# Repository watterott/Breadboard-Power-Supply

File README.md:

# Breadboard Power Supply
Power supply for Breadboards.

* Power Input: microUSB or 2.1mm DC jack
* 5V 800mA voltage regulator
* 3.3V 800mA voltage regulator
* 3.3V or 5V output selectable with jumper
* Open-Source and released under the [Creative Commons Attribution Share-Alike License](https://creativecommons.org/licenses/by-sa/4.0/).
* **[Documentation on learn.watterott.com](https://learn.watterott.com)**

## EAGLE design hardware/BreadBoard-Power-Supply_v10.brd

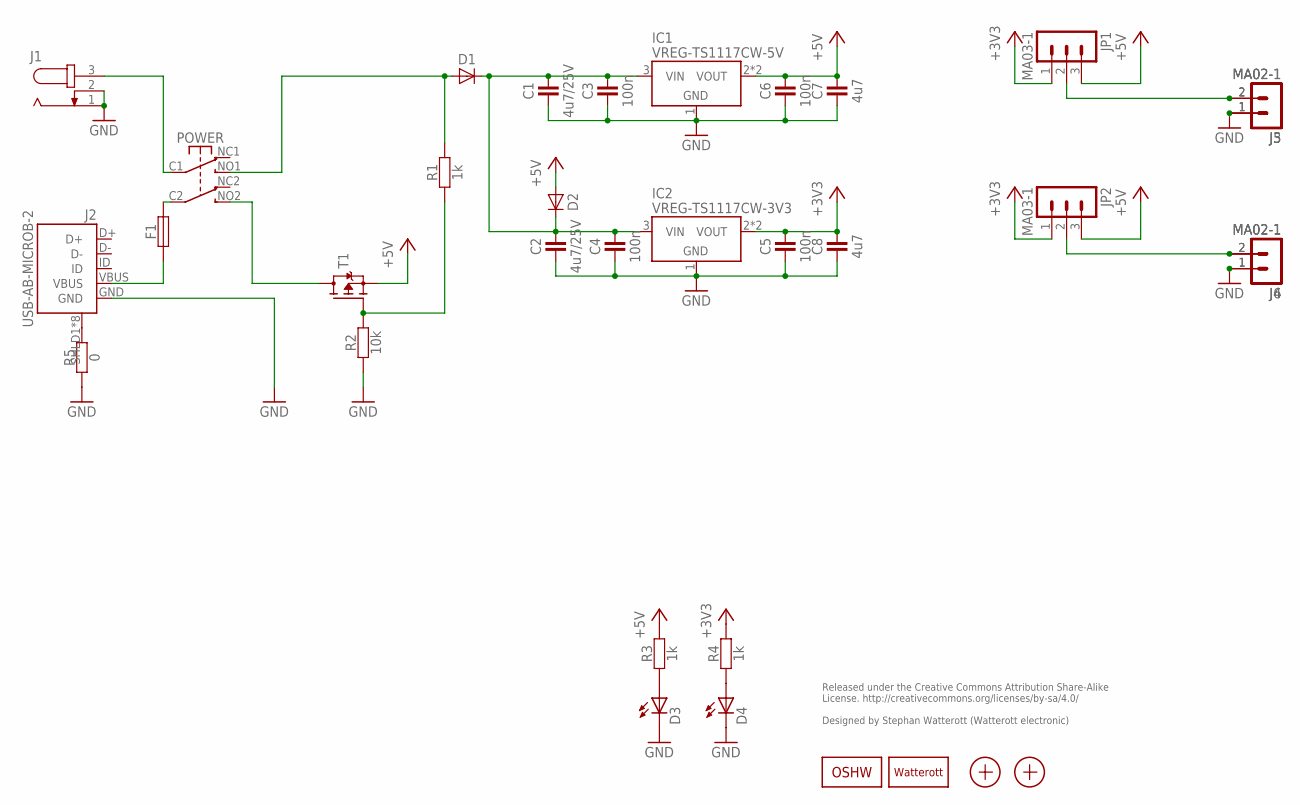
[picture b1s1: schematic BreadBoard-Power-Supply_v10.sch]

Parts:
C1, C2: 4u7/25V; C1206
C3, C4, C5, C6: 100n; C0402
C7, C8: 4u7; C0402
D1, D2: DIODE-SOD80; SOD80
D3, D4: LED-0603; C0603
F1: FUSE-0805; C0805
IC1: VREG-TS1117CW-5V; SOT223
IC2: VREG-TS1117CW-3V3; SOT223
J1: DC-JACK-2.1; DC-JACK
J2: USB-AB-MICROB-2; USB-MICROB-10118194
J3, J4, J5, J6: MA02-1
JP1, JP2: MA03-1
LOGO1: OSHW_LOGOX0070; OSHW_6X70
LOGO2: LOGO-PLACE; LOGO_TPLACE
POWER: SW-2UMGF1260159; GF1260159
R1, R3, R4: 1k; C0402
R2: 10k; C0402
R5: 0; C0402
T1: MOSFET-P-SOT23; SOT23
X1, X2: PASSER-07; PASSER_07MM

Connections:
+3V3: C5.2, C8.2, IC2.2 (VOUT), IC2.4 (VOUT), JP1.1, JP2.1, R4.2
+5V: C6.2, C7.2, D2.A, IC1.2 (VOUT), IC1.4 (VOUT), JP1.3, JP2.3, R3.2, T1.2 (S)
GND: C1.1, C2.1, C3.1, C4.1, C5.1, C6.1, C7.1, C8.1, D3.C, D4.C, IC1.1 (GND), IC2.1 (GND), J1.1, J1.2, J2.GND, J3.1, J4.1, J5.1, J6.1, R2.1, R5.1
unnamed: D1.A, POWER.NO1 (S1), R1.2
unnamed: J1.3, POWER.C1 (P1)
unnamed: R1.1, R2.2, T1.1 (G)
unnamed: POWER.NO2 (S2), T1.3 (D)
unnamed: D3.A, R3.1
unnamed: D4.A, R4.1
unnamed: J3.2, J5.2, JP1.2
unnamed: J4.2, J6.2, JP2.2
unnamed: F1.2, POWER.C2 (P2)
unnamed: J2.SHLD1 (SHIELD), J2.SHLD2 (SHIELD), J2.SHLD3 (SHIELD), J2.SHLD4 (SHIELD), J2.SHLD5 (SHIELD), J2.SHLD6 (SHIELD), J2.SHLD7 (SHIELD), J2.SHLD8 (SHIELD), R5.2
VBUS: F1.1, J2.VBUS
VIN: C1.2, C2.2, C3.2, C4.2, D1.C, D2.C, IC1.3 (VIN), IC2.3 (VIN)

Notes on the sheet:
Released under the Creative Commons Attribution Share-Alike License. http://creativecommons.org/licenses/by-sa/4.0/ Designed by Stephan Watterott (Watterott electronic)

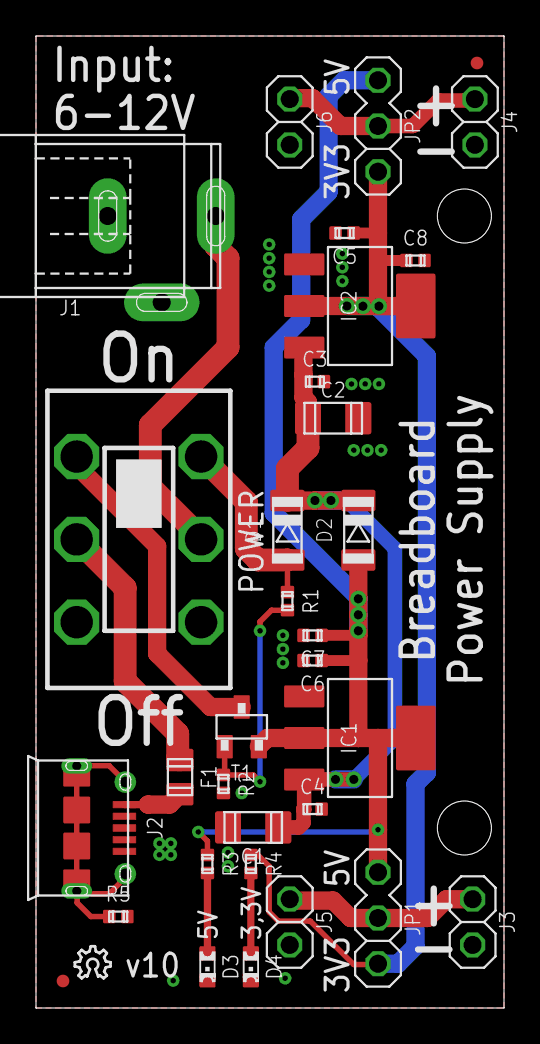
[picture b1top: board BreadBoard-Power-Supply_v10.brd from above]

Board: 2 copper layers, 26.0 x 54.0 mm, 34 parts (1 on the bottom side), 15 nets.
